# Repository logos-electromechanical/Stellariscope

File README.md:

Stellariscope
=============

My TI Boosterpack entry -- a driver for 8x8 RGB LED arrays that can be plugged into arrays.

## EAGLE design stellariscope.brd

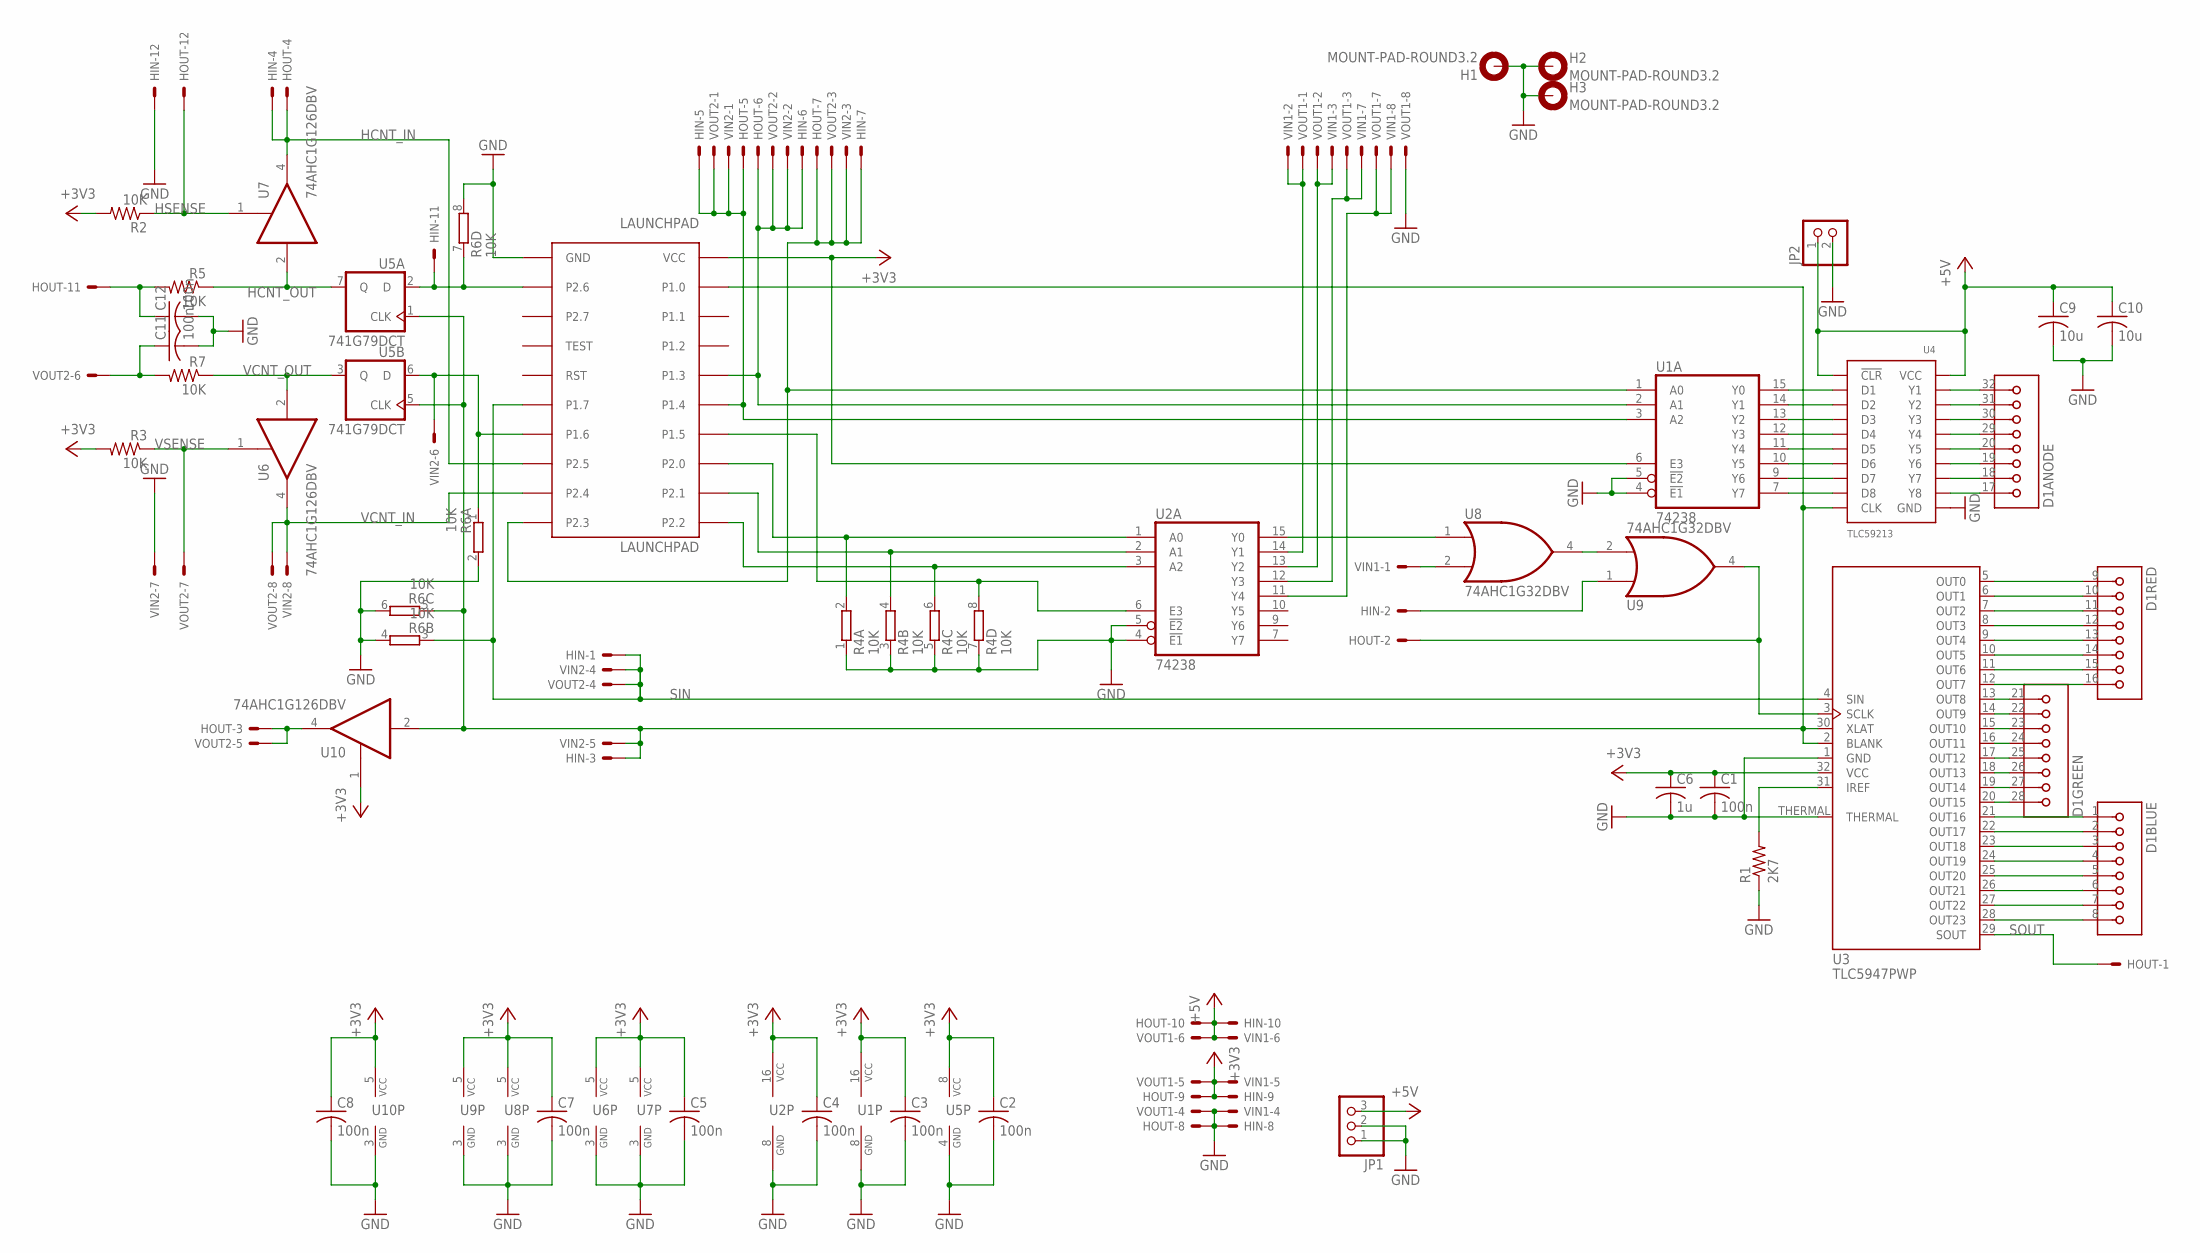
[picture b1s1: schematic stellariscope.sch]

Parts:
C1, C2, C3, C4, C5, C7, C8, C11, C12: 100n; C0603; PARTNO CC0603KRX7R9BB104
C6: 1u; C0603; PARTNO C1608X5R1E105M
C9, C10: 10u; C1210; PARTNO C3216X5R1E106M
D1: 60MM-8X8-RGB-LED-ARRAY; 60MM-8X8-RGB-MATRIX; PARTNO *
H1, H2, H3: MOUNT-PAD-ROUND3.2; 3,2-PAD
HIN: 87760-121; PARTNO 87760-121
HOUT: 87264-125; PARTNO 87264-125
JP1: PINHD-1X3; 1X03; PARTNO *
JP2: PINHD-1X2_2.54-90°; 1X02/90; PARTNO *
LAUNCHPAD: LAUNCHPAD
R1: 2K7; R0603; PARTNO RMCF0603FT2K70
R2, R3, R5, R7: 10K; R0603; PARTNO RMCF0603FT10K0
R4, R6: 10K; CTS742C083-RES; PARTNO 742C083103JPTR
U1, U2: 74238; TSSOP16; PARTNO CD74HC238PWR
U3: TLC5947PWP; HTSSOP32-PWP; PARTNO TLC5947DAP
U4: TLC59213; TSSOP20; PARTNO TLC59213IPWR
U5: 741G79DCT; DCT_R-PDSO-G8; PARTNO SN74LVC2G79DCTR
U6, U7, U10: 74AHC1G126DBV; SOT23-5; PARTNO SN74LVC1G126DBVR
U8, U9: 74AHC1G32DBV; SOT23-5; PARTNO SN74LVC1G32QDBVRQ1
VIN1, VIN2: 87760-081; PARTNO 87760-081
VOUT1, VOUT2: 87264-085; PARTNO 87264-085

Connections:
+3V3: C1.1, C2.1, C3.1, C4.1, C5.1, C6.1, C7.1, C8.1, HIN.10, HOUT.9, LAUNCHPAD.VCC, R2.2, R3.2, U1.6 (E3), U1.16 (VCC), U2.16 (VCC), U3.32 (VCC), U5.8 (VCC), U6.5 (VCC), U7.5 (VCC), U8.5 (VCC), U9.5 (VCC), U10.1 (OE), U10.5 (VCC), VIN1.5, VOUT1.5
+5V: C9.1, C10.1, HIN.9, HOUT.10, JP1.3, JP2.1, U4.1 (!CLR!), U4.20 (VCC), VIN1.6, VOUT1.6
D1: U1.15 (Y0), U4.2 (D1)
D2: U1.14 (Y1), U4.3 (D2)
D3: U1.13 (Y2), U4.4 (D3)
D4: U1.12 (Y3), U4.5 (D4)
D5: U1.11 (Y4), U4.6 (D5)
D6: U1.10 (Y5), U4.7 (D6)
D7: U1.9 (Y6), U4.8 (D7)
D8: U1.7 (Y7), U4.9 (D8)
GND: C1.2, C2.2, C3.2, C4.2, C5.2, C6.2, C7.2, C8.2, C9.2, C10.2, C11.2, C12.2, H1.B3,2, H2.B3,2, H3.B3,2, HIN.8, HIN.12, HOUT.8, JP1.1, JP1.2, JP2.2, LAUNCHPAD.GND, R1.1, R4.1, R4.3 (1), R4.5 (1), R4.7 (1), R6.2, R6.4 (2), R6.6 (2), R6.8 (2), U1.4 (!E1!), U1.5 (!E2!), U1.8 (GND), U2.4 (!E1!), U2.5 (!E2!), U2.8 (GND), U3.1 (GND), U3.THERMAL, U4.11 (GND), U5.4 (GND), U6.3 (GND), U7.3 (GND), U8.3 (GND), U9.3 (GND), U10.3 (GND), VIN1.4, VIN2.7, VOUT1.4, VOUT1.8
HCNT_IN: HIN.4, HOUT.4, LAUNCHPAD.P2.5, U7.4 (O)
HCNT_OUT: R5.1, U5.7 (Q), U7.2 (I)
HSENSE: HOUT.12, R2.1, U7.1 (OE)
unnamed: D1.9 (1), U3.5 (OUT0)
unnamed: D1.10 (2), U3.6 (OUT1)
unnamed: D1.11 (3), U3.7 (OUT2)
unnamed: D1.12 (4), U3.8 (OUT3)
unnamed: D1.13 (5), U3.9 (OUT4)
unnamed: D1.14 (6), U3.10 (OUT5)
unnamed: D1.15 (7), U3.11 (OUT6)
unnamed: D1.16 (8), U3.12 (OUT7)
unnamed: D1.28 (1), U3.20 (OUT15)
unnamed: D1.27 (2), U3.19 (OUT14)
unnamed: D1.26 (3), U3.18 (OUT13)
unnamed: D1.25 (4), U3.17 (OUT12)
unnamed: D1.24 (5), U3.16 (OUT11)
unnamed: D1.23 (6), U3.15 (OUT10)
unnamed: D1.22 (7), U3.14 (OUT9)
unnamed: D1.21 (8), U3.13 (OUT8)
unnamed: D1.1, U3.21 (OUT16)
unnamed: D1.2, U3.22 (OUT17)
unnamed: D1.3, U3.23 (OUT18)
unnamed: D1.4, U3.24 (OUT19)
unnamed: D1.5, U3.25 (OUT20)
unnamed: D1.6, U3.26 (OUT21)
unnamed: D1.7, U3.27 (OUT22)
unnamed: D1.8, U3.28 (OUT23)
unnamed: HIN.2, U9.1 (I0)
unnamed: R1.2, U3.31 (IREF)
unnamed: U2.12 (Y3), VIN1.7, VOUT1.3
unnamed: C12.1, HOUT.11, R5.2
unnamed: LAUNCHPAD.P1.5, R4.8 (2), U2.6 (E3)
unnamed: U2.15 (Y0), U8.1 (I0)
unnamed: LAUNCHPAD.P2.0, R4.2, U2.1 (A0)
unnamed: LAUNCHPAD.P2.1, R4.4 (2), U2.2 (A1)
unnamed: LAUNCHPAD.P2.2, R4.6 (2), U2.3 (A2)
unnamed: HIN.5, HOUT.5, LAUNCHPAD.P1.4, U1.3 (A2), VIN2.1, VOUT2.1
unnamed: HIN.6, HOUT.6, LAUNCHPAD.P1.3, U1.2 (A1), VIN2.2, VOUT2.2
unnamed: HIN.7, HOUT.7, LAUNCHPAD.P2.3, U1.1 (A0), VIN2.3, VOUT2.3
unnamed: HIN.11, LAUNCHPAD.P2.6, R6.7 (1), U5.2 (D)
unnamed: LAUNCHPAD.P1.6, R6.1, U5.6 (D), VIN2.6
unnamed: U2.14 (Y1), VIN1.2, VOUT1.1
unnamed: U2.13 (Y2), VIN1.3, VOUT1.2
unnamed: U2.11 (Y4), VIN1.8, VOUT1.7
unnamed: C11.1, R7.2, VOUT2.6
unnamed: U8.2 (I1), VIN1.1
unnamed: U8.4 (O), U9.2 (I1)
unnamed: HOUT.2, U3.3 (SCLK), U9.4 (O)
SIN: HIN.1, LAUNCHPAD.P1.7, R6.3 (1), U3.4 (SIN), VIN2.4, VOUT2.4
SOUT: HOUT.1, U3.29 (SOUT)
VCNT_IN: LAUNCHPAD.P2.4, U6.4 (O), VIN2.8, VOUT2.8
VCNT_OUT: R7.1, U5.3 (Q), U6.2 (I)
VSENSE: R3.1, U6.1 (OE), VOUT2.7
XLAT: HIN.3, LAUNCHPAD.P1.0, R6.5 (1), U3.2 (BLANK), U3.30 (XLAT), U4.10 (CLK), U5.1 (CLK), U5.5 (CLK), U10.2 (I), VIN2.5
XLAT_OUT: HOUT.3, U10.4 (O), VOUT2.5
Y1: D1.32 (8), U4.19 (Y1)
Y2: D1.31 (7), U4.18 (Y2)
Y3: D1.30 (6), U4.17 (Y3)
Y4: D1.29 (5), U4.16 (Y4)
Y5: D1.20 (4), U4.15 (Y5)
Y6: D1.19 (3), U4.14 (Y6)
Y7: D1.18 (2), U4.13 (Y7)
Y8: D1.17 (1), U4.12 (Y8)

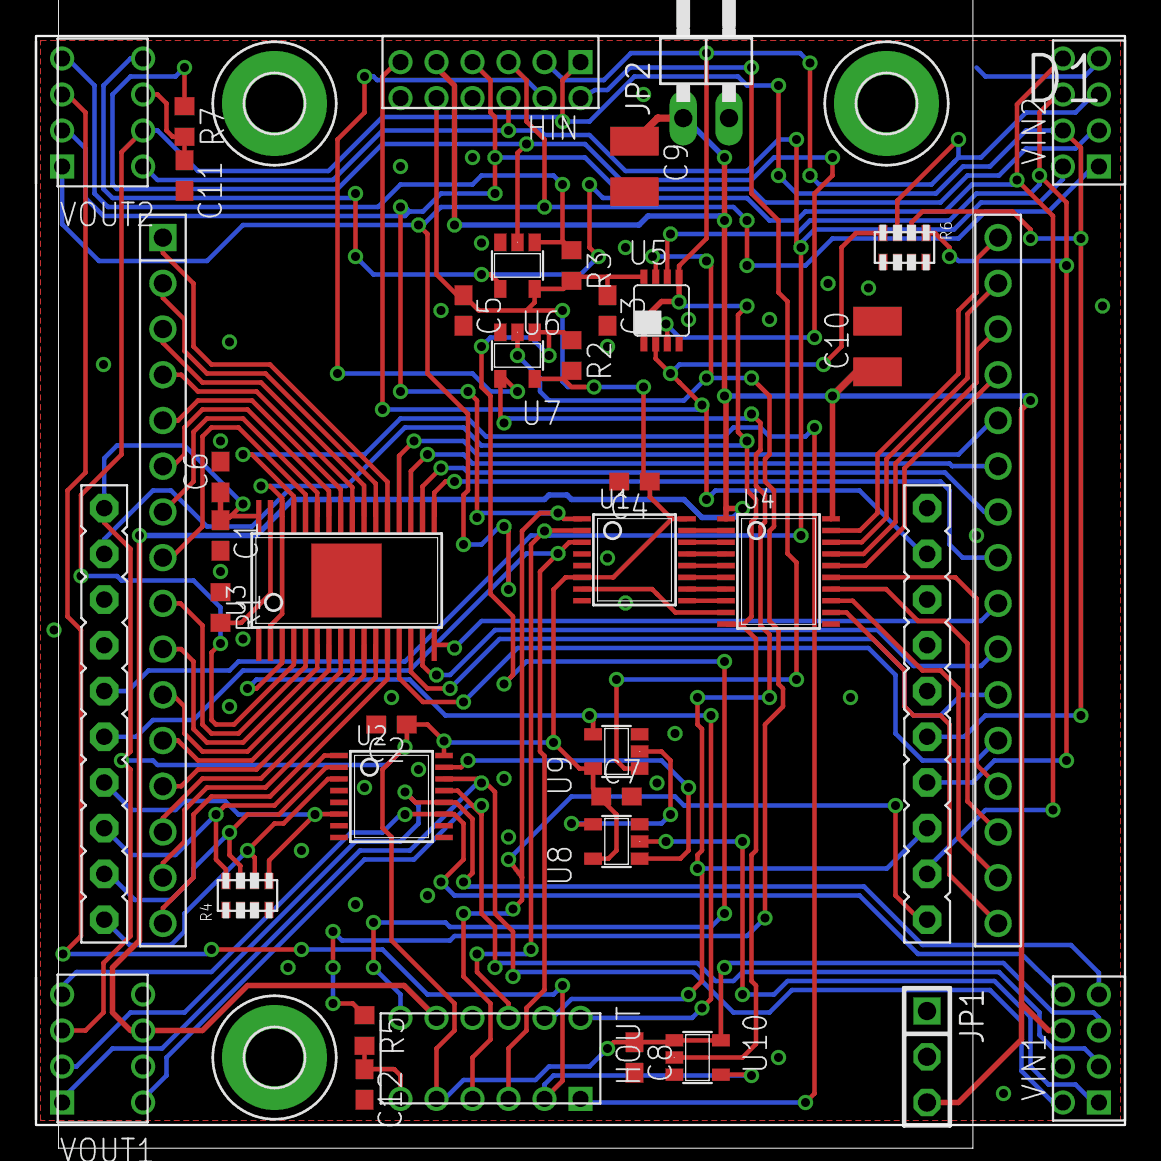
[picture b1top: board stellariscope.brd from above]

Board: 2 copper layers, 60.5 x 60.5 mm, 42 parts (0 on the bottom side), 74 nets.

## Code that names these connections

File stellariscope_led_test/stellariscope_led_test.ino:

#include <SPI.h>

// pin definitions
const int latch     = P1_0;  // latch signal 
const int col0      = P1_2;  // column select bit 0
const int col1      = P1_3;  // column select bit 1
const int col2      = P1_4;  // column select bit 2
const int clkadd0   = P2_0;  // module row select bit 0
const int clkadd1   = P2_1;  // module row select bit 1
const int clkadd2   = P2_2;  // module row select bit 2
const int hcnt_out  = P2_6;  // horizontal count output
const int vcnt_out  = P1_6;  // vertical count output
const int hcnt_in   = P2_5;  // horizontal count return
const int vcnt_in   = P2_4;  // vertical count return

void setup() {
  // initialize pins
  pinMode (latch, OUTPUT);
  pinMode (col0, OUTPUT);
  pinMode (col1, OUTPUT);
  pinMode (col2, OUTPUT);
  pinMode (clkadd0, OUTPUT);
  pinMode (clkadd1, OUTPUT);
  pinMode (clkadd2, OUTPUT);
  pinMode (hcnt_out, OUTPUT);
  pinMode (vcnt_out, OUTPUT);
  pinMode (hcnt_in, INPUT);
  pinMode (vcnt_in, INPUT);
  digitalWrite (latch, LOW);
  digitalWrite (hcnt_out, HIGH);
  digitalWrite (vcnt_out, HIGH);
  digitalWrite (clkadd0, LOW);
  digitalWrite (clkadd1, LOW);
  digitalWrite (clkadd2, LOW);
  // initialize SPI:
  SPI.begin(); 
  SPI.setBitOrder(LSBFIRST);
}

void loop() {
  int i, j;
  digitalWrite(clkadd0, LOW);
  digitalWrite(clkadd1, LOW);
  digitalWrite(clkadd2, LOW);
  for (i = 0; i < 8; i++) {
    digitalWrite(latch, LOW);
    //if (i < 4) {
      for (j = 0; j < 12; j++) {
        //if ((j < 8) && (j >= 4)) { 
          SPI.transfer(0x02);
          SPI.transfer(0x20);
          SPI.transfer(0x22);
        //} else {
          //SPI.transfer(0x00);
          //SPI.transfer(0x00);
          //SPI.transfer(0x00);
        //} 
      }
    /*} else {
      for (j = 0; j < 18; j++) {
        SPI.transfer(0);
        SPI.transfer(0);
      }
    }*/
    if (i & 1) {
      digitalWrite(col0, HIGH);
    } else {
      digitalWrite(col0, LOW);
    }
    if (i & 2) {
      digitalWrite(col1, HIGH);
    } else {
      digitalWrite(col1, LOW);
    }
    if (i & 4) {
      digitalWrite(col2, HIGH);
    } else {
      digitalWrite(col2, LOW);
    }
    digitalWrite(latch, HIGH);
    digitalWrite(latch, LOW);
  }
  //delay(100);
}

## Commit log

2013-02-21 Adding original Stellariscope design. This is the one the prototypes were built from.
2013-02-21 This update fixes the issues with the board counting logic in the first edition. It also adds a driver to the XLAT line in order to prevent fanout problems in large array. This version has not been b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
2013-02-22 -- Rotated Launchpad footprint to align with LED array -- Swapped vertical connectors to improve routing post-rotation -- Switched power on TLC5947 to 3V3, in order to accomodate logic levels -- Relo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
2013-02-22 -- Added initial test code
2013-03-01 -- Moved the old demo code to led test -- First commit of new demo code -- Updated hardware design -- Add 10 uF decoupling caps for board & anode drive -- tied latch and blank lines together
2013-03-02 -- Modified pinout to allow UART to function correctly
2013-03-02 Fixed the serial issue right this time, miscellaneous test code changes (not done)
2013-03-02 Demo software used during video
2013-06-16 -- added pull-downs to all inputs from the Launchpad -- added delay filters to counting lines so they work now.
2013-12-27 Committing everything to date...

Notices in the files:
parts and their libraries:
SparkFun-Aesthetics: Licensing: CC v3.0 Share-Alike You are welcome to use this library for commercial purposes.
